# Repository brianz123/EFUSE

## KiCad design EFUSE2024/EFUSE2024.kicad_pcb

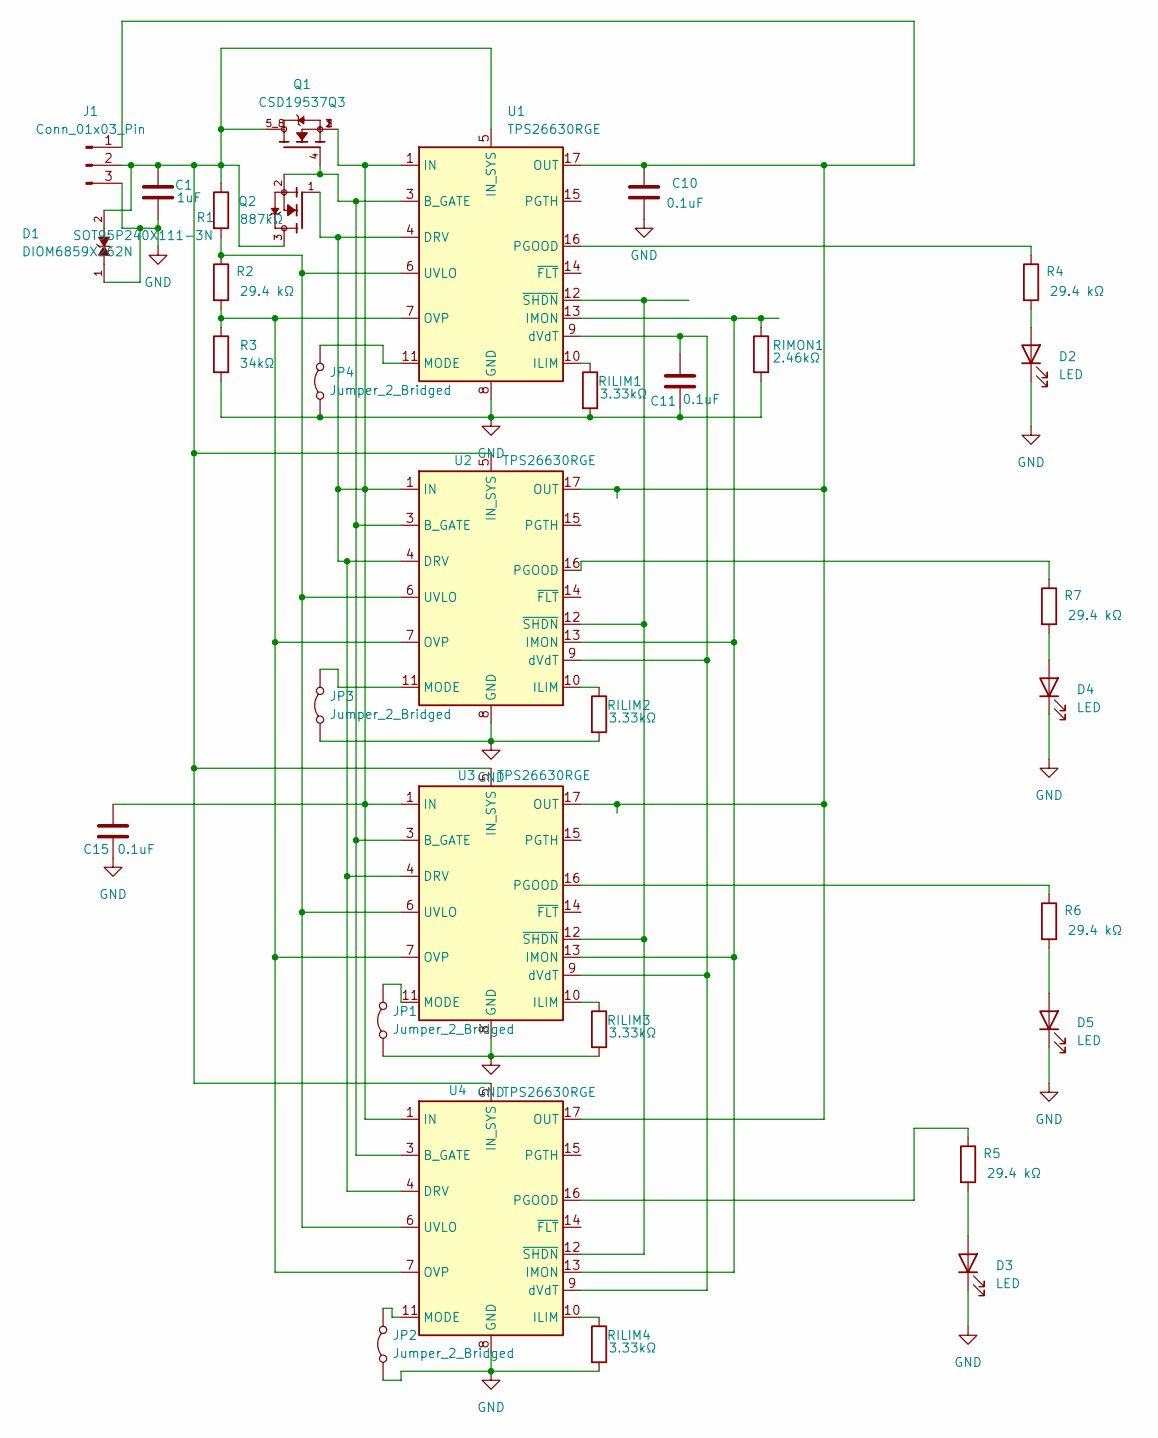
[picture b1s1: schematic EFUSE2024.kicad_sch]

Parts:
C1: 1uF; C_0805_2012Metric_Pad1.18x1.45mm_HandSolder
C10, C11, C15: 0.1uF; C_0805_2012Metric_Pad1.18x1.45mm_HandSolder
D1: DIOM6859X262N; SMCJ36CA; PARTREV R2102
D2, D3, D4, D5: LED; LED_1206_3216Metric_Pad1.42x1.75mm_HandSolder
J1: Conn_01x03_Pin; SolderWire-1.5sqmm_1x03_P7.8mm_D1.7mm_OD3.9mm
JP1, JP2, JP3, JP4: Jumper_2_Bridged; SolderJumper-2_P1.3mm_Bridged2Bar_Pad1.0x1.5mm
Q1: CSD19537Q3; TRANS_CSD19537Q3; PARTREV A
Q2: SOT95P240X111-3N; BSS138; PARTREV 30 Jan 2018
R1: 887kΩ; R_0805_2012Metric_Pad1.20x1.40mm_HandSolder
R2, R4, R5, R6, R7: 29.4 kΩ; R_0805_2012Metric_Pad1.20x1.40mm_HandSolder
R3: 34kΩ; R_0805_2012Metric_Pad1.20x1.40mm_HandSolder
RILIM1, RILIM2, RILIM3, RILIM4: 3.33kΩ; R_0805_2012Metric_Pad1.20x1.40mm_HandSolder
RIMON1: 2.46kΩ; R_0805_2012Metric_Pad1.20x1.40mm_HandSolder
U1, U2, U3, U4: TPS26630RGE; QFN50P400X400X100-25N

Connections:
GND: C1.2, C10.2, C11.2, C15.2, D1.1, D2.1 (K), D3.1 (K), D4.1 (K), D5.1 (K), J1.3, JP1.1 (A), JP2.1 (A), JP3.1 (A), JP4.1 (A), R3.2, RILIM1.2, RILIM2.2, RILIM3.2, RILIM4.2, RIMON1.2, U1.8 (GND), U1.25 (GND), U2.8 (GND), U2.25 (GND), U3.8 (GND), U3.25 (GND), U4.8 (GND), U4.25 (GND)
unnamed: D2.2 (A), R4.2
unnamed: D3.2 (A), R5.2
unnamed: D4.2 (A), R7.2
unnamed: D5.2 (A), R6.2
unnamed: C10.1, J1.1, U1.17 (OUT), U1.18 (OUT), U2.17 (OUT), U2.18 (OUT), U3.17 (OUT), U3.18 (OUT), U4.17 (OUT), U4.18 (OUT)
unnamed: C1.1, D1.2, J1.2, Q1.5_8, Q2.3, R1.1, U1.5 (IN_SYS), U2.5 (IN_SYS), U3.5 (IN_SYS), U4.5 (IN_SYS)
unnamed: JP1.2 (B), U3.11 (MODE)
unnamed: JP2.2 (B), U4.11 (MODE)
unnamed: JP3.2 (B), U2.11 (MODE)
unnamed: JP4.2 (B), U1.11 (MODE)
unnamed: Q1.4, Q2.2, U1.3 (B_GATE), U2.3 (B_GATE), U3.3 (B_GATE), U4.3 (B_GATE)
unnamed: C15.1, Q1.1, Q1.2, Q1.3, Q2.1, U1.1 (IN), U1.2 (IN), U1.4 (DRV), U2.1 (IN), U2.2 (IN), U2.4 (DRV), U3.1 (IN), U3.2 (IN), U3.4 (DRV), U4.1 (IN), U4.2 (IN), U4.4 (DRV)
unnamed: RILIM1.1, U1.10 (ILIM)
unnamed: RIMON1.1, U1.13 (IMON), U2.13 (IMON), U3.13 (IMON), U4.13 (IMON)
unnamed: R2.2, R3.1, U1.7 (OVP), U2.7 (OVP), U3.7 (OVP), U4.7 (OVP)
unnamed: R4.1, U1.16 (PGOOD)
unnamed: R1.2, R2.1, U1.6 (UVLO), U2.6 (UVLO), U3.6 (UVLO), U4.6 (UVLO)
unnamed: C11.1, U1.9 (dVdT), U2.9 (dVdT), U3.9 (dVdT), U4.9 (dVdT)
unnamed: U1.12 (~SHDN), U2.12 (~SHDN), U3.12 (~SHDN), U4.12 (~SHDN)
unnamed: RILIM2.1, U2.10 (ILIM)
unnamed: R7.1, U2.16 (PGOOD)
unnamed: RILIM3.1, U3.10 (ILIM)
unnamed: R6.1, U3.16 (PGOOD)
unnamed: RILIM4.1, U4.10 (ILIM)
unnamed: R5.1, U4.16 (PGOOD)

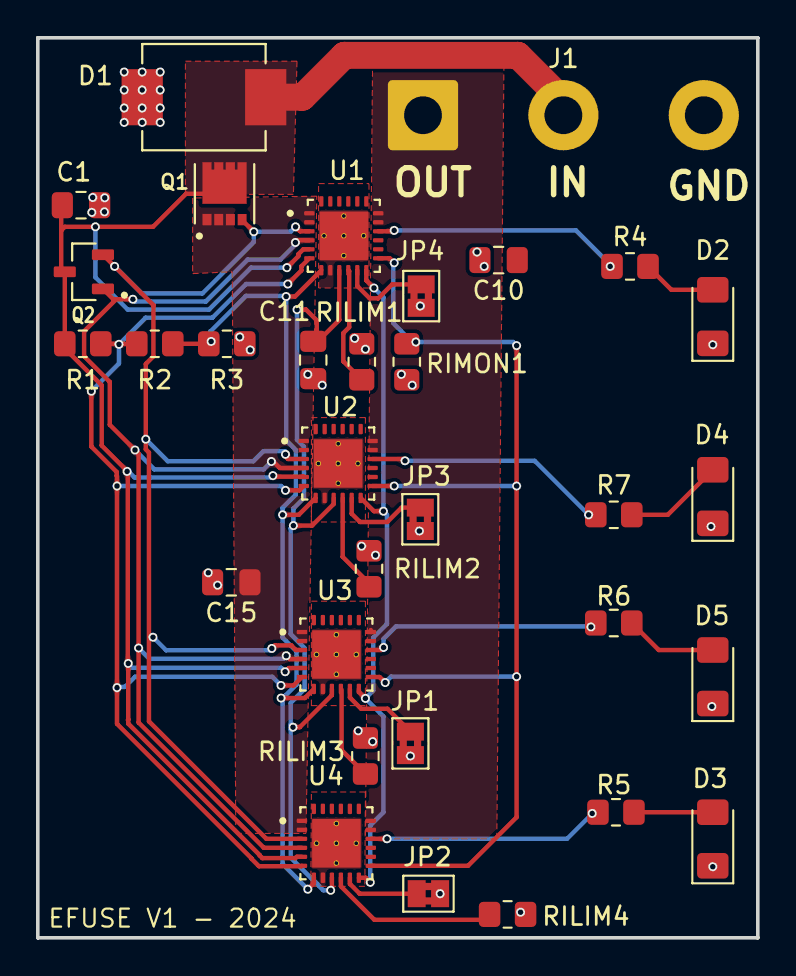
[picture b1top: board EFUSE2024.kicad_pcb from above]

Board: 2 copper layers, 40.0 x 50.0 mm, 32 parts (0 on the bottom side), 26 nets.

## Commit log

2024-10-31 test3
2024-10-31 test5
2024-10-31 test
2024-10-31 added efuse components
2024-10-31 added efuses
2024-11-07 test
    something
2024-11-07 adding TPS16630 files
2024-11-07 For Nitya
2024-11-07 nvfnv
2024-11-07 fixed
2024-11-07 Revert "fixed"
    This reverts commit 7d00a26f4489b6db16a76b6609abb19c4e55ea70.
2024-11-07 fix schematic
2024-11-10 schematic
2024-11-10 Adding to schematic
2024-11-10 asjdflk
2024-11-10 deleted two
2024-11-10 added connector
2024-11-10 Added footprints
2024-11-10 Updated schematic values
2024-11-10 ADDED LEDS
2024-11-10 added footprint
2024-11-17 updates from Brian
2024-11-17 PBC changes
2024-11-21 PBC - brian help
2024-11-22 fixed up PCB
2024-11-23 adding gerber files
2024-12-01 add jumpers
2024-12-01 update jumpers
2024-12-01 final update
2024-12-01 cleanup
2024-12-01 last Update(for real!)
